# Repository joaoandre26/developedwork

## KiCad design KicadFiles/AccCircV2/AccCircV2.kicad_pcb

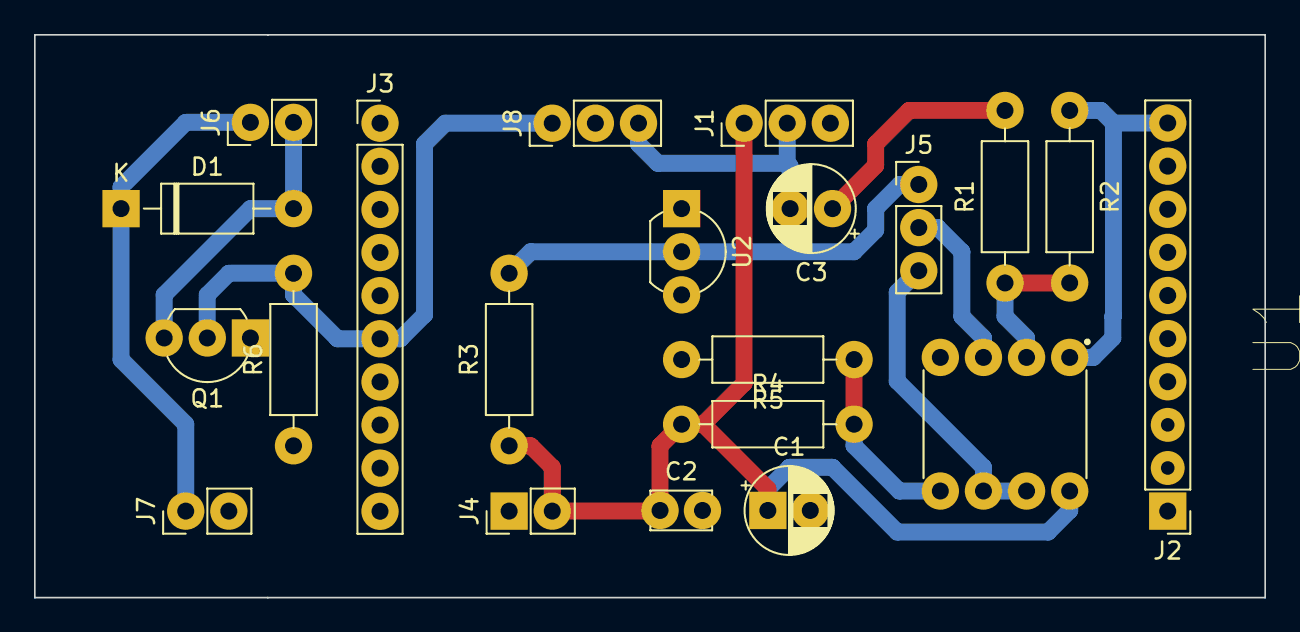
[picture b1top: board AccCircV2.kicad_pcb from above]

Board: 2 copper layers, 72.5 x 33.2 mm, 21 parts (0 on the bottom side), 13 nets.

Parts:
C1, C3: 10uF; CP_Radial_D5.0mm_P2.50mm
C2: 1nF; C_Disc_D3.4mm_W2.1mm_P2.50mm
D1: 1N4001; D_DO-41_SOD81_P10.16mm_Horizontal
J1: AccelConnector; PinHeader_1x03_P2.54mm_Vertical
J2: ADCInput; PinHeader_1x10_P2.54mm_Vertical
J3: IO; PinHeader_1x10_P2.54mm_Vertical
J4: ExternalSupply3V3; PinHeader_1x02_P2.54mm_Vertical
J5: VoltageRefSel; PinHeader_1x03_P2.54mm_Vertical
J6: Solenoid Connector; PinHeader_1x02_P2.54mm_Vertical
J7: ExternalSupply5V; PinHeader_1x02_P2.54mm_Vertical
J8: ControlSig; PinHeader_1x03_P2.54mm_Vertical
Q1: TN0207; TO-92L_Inline_Wide
R1, R2, R4, R5: R; R_Axial_DIN0207_L6.3mm_D2.5mm_P10.16mm_Horizontal
R3: 180k; R_Axial_DIN0207_L6.3mm_D2.5mm_P10.16mm_Horizontal
R6: 10k; R_Axial_DIN0207_L6.3mm_D2.5mm_P10.16mm_Horizontal
U1: MCP602; DIP787W46P254L927H533Q8
U2: LM385Z-ADJ; TO-92_Inline_Wide

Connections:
+3V3: C1.1, C2.1, J1.1, J4.2, R3.1, R4.1, U1.8
+5V: D1.1, J6.1, J7.1
AccSignal: C3.2, J1.2, J8.3
GND: C1.2, C2.2, J1.3, J3.10, J4.1, J7.2, J8.2, Q1.1, R5.2, R6.1, U1.4, U2.1, U2.3
unnamed: C3.1, R1.2
unnamed: D1.2, J6.2, Q1.3
unnamed: J2.10, R2.1, U1.1
unnamed: J5.2, U1.3
unnamed: R1.1, R2.2, U1.2
unnamed: R4.2, R5.1, U1.5
PIN3.2: J3.6, J8.1, Q1.2, R6.2
VolDivider: J5.3, U1.6, U1.7
VolRef1V2: J5.1, R3.2, U2.2

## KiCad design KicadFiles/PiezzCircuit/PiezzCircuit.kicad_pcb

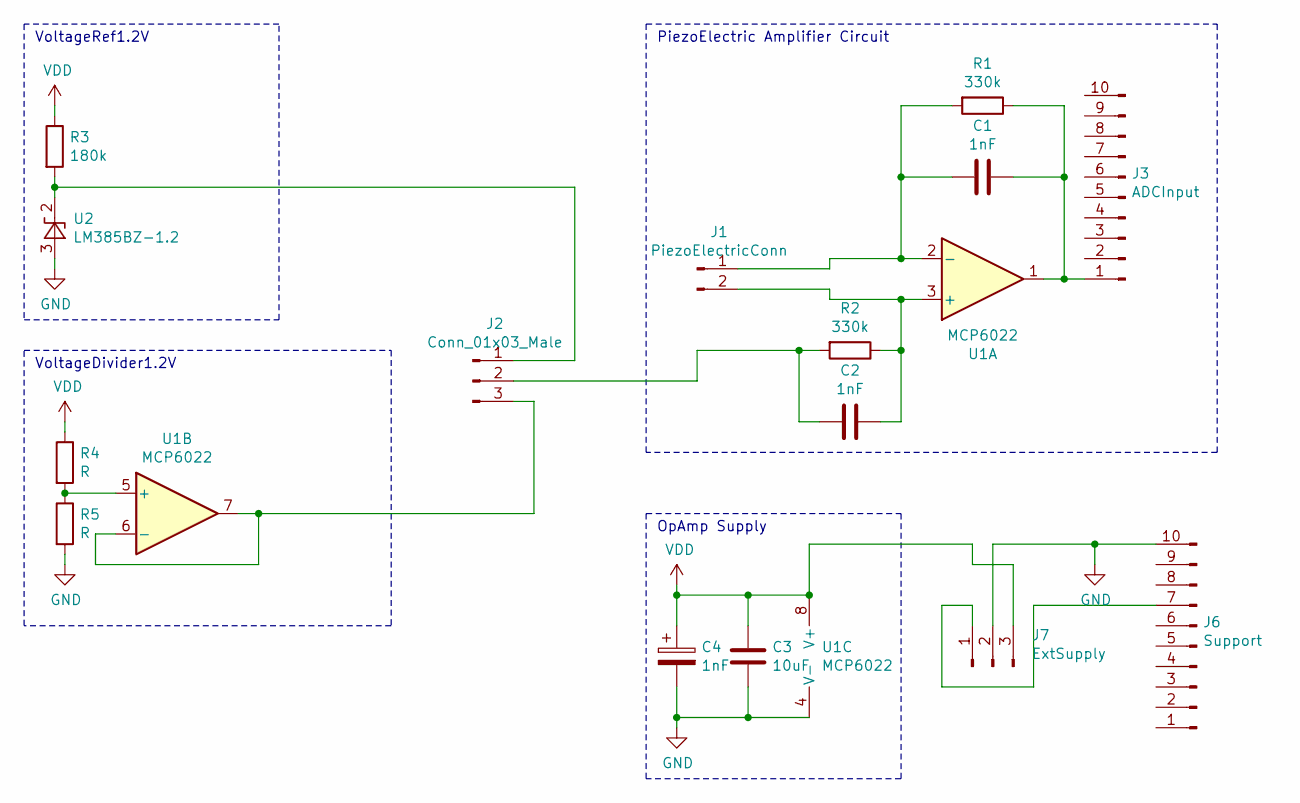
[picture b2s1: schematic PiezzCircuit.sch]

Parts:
C1, C2: 1nF; C_Rect_L4.0mm_W2.5mm_P2.50mm
C3: 10uF; C_Rect_L4.0mm_W2.5mm_P2.50mm
C4: 1nF; CP_Radial_D5.0mm_P2.00mm
J1: PiezoElectricConn; PinHeader_1x02_P2.54mm_Vertical
J2: Conn_01x03_Male; PinHeader_1x03_P2.54mm_Vertical
J3: ADCInput; PinHeader_1x10_P2.54mm_Vertical
J6: Support; PinHeader_1x10_P2.54mm_Vertical
J7: ExtSupply; PinHeader_1x03_P2.54mm_Horizontal
R1, R2: 330k; R_Axial_DIN0207_L6.3mm_D2.5mm_P10.16mm_Horizontal
R3: 180k; R_Axial_DIN0207_L6.3mm_D2.5mm_P7.62mm_Horizontal
R4, R5: R; R_Axial_DIN0207_L6.3mm_D2.5mm_P10.16mm_Horizontal
U1: MCP6022; DIP787W46P254L927H533Q8
U2: LM385BZ-1.2; TO-92_Inline

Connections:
GND: C3.2, C4.2, J6.10, J7.2, R5.2, U1.4 (V-), U2.3 (A)
unnamed: C1.1, J3.1, R1.1, U1.1
unnamed: C1.2, J1.1, R1.2, U1.2 (-)
unnamed: C2.1, J1.2, R2.1, U1.3 (+)
unnamed: C2.2, J2.2, R2.2
unnamed: J2.1, R3.2, U2.2 (K)
unnamed: J2.3, U1.6 (-), U1.7
unnamed: J6.7, J7.1
unnamed: R4.2, R5.1, U1.5 (+)
VDD: C3.1, C4.1, J7.3, R3.1, R4.1, U1.8 (V+)

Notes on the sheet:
VoltageRef1.2V
VoltageDivider1.2V
PiezoElectric Amplifier Circuit
OpAmp Supply

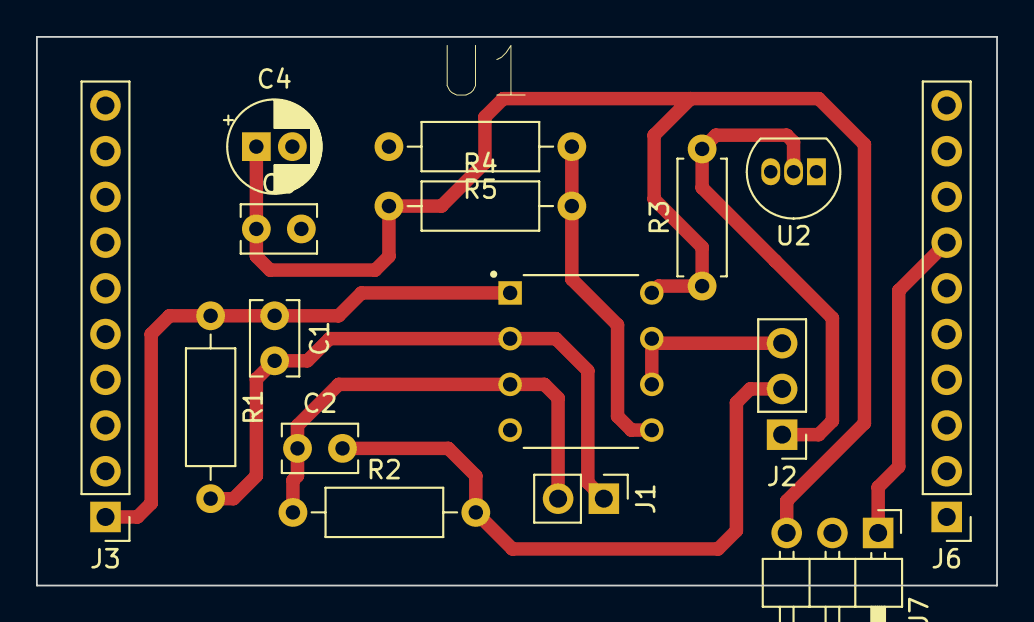
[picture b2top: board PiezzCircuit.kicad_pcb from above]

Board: 2 copper layers, 53.3 x 30.5 mm, 16 parts (0 on the bottom side), 10 nets.

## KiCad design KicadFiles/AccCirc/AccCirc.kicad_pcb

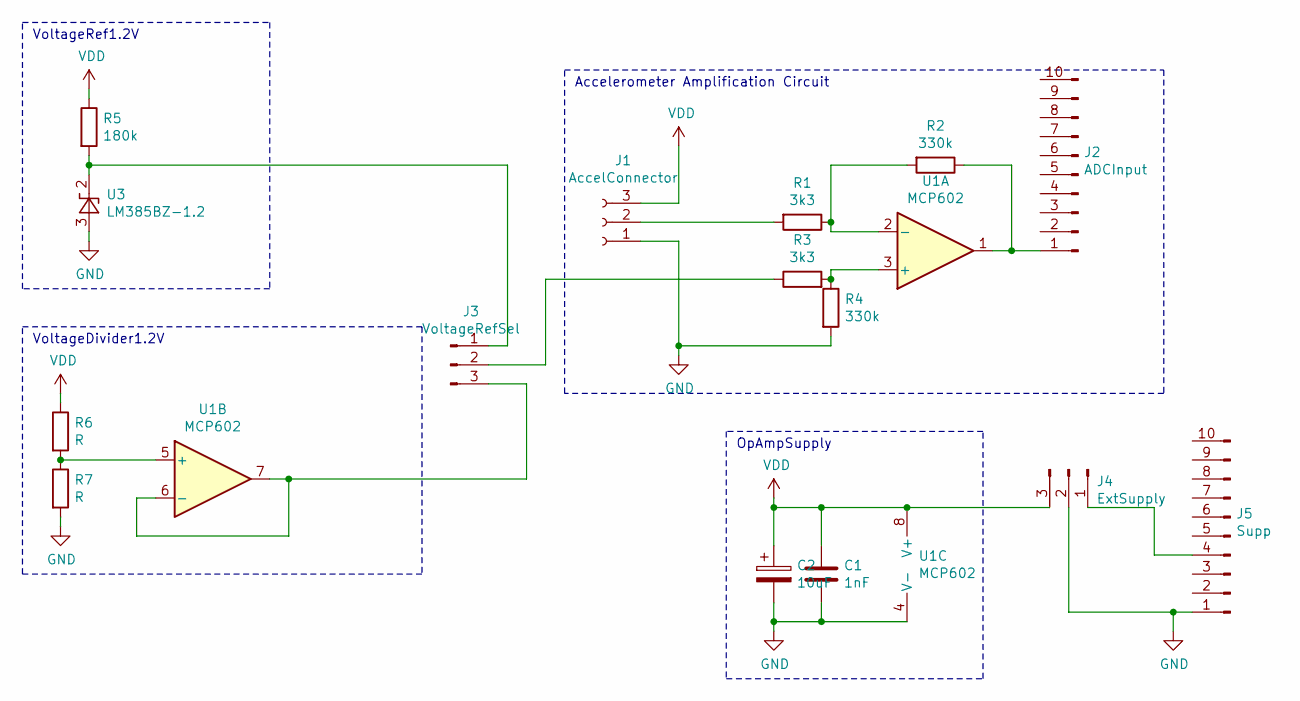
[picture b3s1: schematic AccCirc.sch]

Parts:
C1: 1nF; C_Disc_D10.5mm_W5.0mm_P5.00mm
C2: 10uF; C_Radial_D5.0mm_H11.0mm_P2.00mm
J1: AccelConnector; PinSocket_1x03_P2.54mm_Horizontal
J2: ADCInput; PinHeader_1x10_P2.54mm_Vertical
J3: VoltageRefSel; PinHeader_1x03_P2.54mm_Vertical
J4: ExtSupply; PinSocket_1x03_P2.54mm_Horizontal
J5: Supp; PinHeader_1x10_P2.54mm_Vertical
R1, R3: 3k3; R_Axial_DIN0207_L6.3mm_D2.5mm_P10.16mm_Horizontal
R2, R4: 330k; R_Axial_DIN0207_L6.3mm_D2.5mm_P10.16mm_Horizontal
R5: 180k; R_Axial_DIN0207_L6.3mm_D2.5mm_P10.16mm_Horizontal
R6, R7: R; R_Axial_DIN0207_L6.3mm_D2.5mm_P10.16mm_Horizontal
U1: MCP602; DIP787W46P254L927H533Q8
U3: LM385BZ-1.2; TO-92_Inline

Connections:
GND: C1.2, C2.2, J1.1, J4.2, J5.1, R4.2, R7.2, U1.4 (V-), U3.3 (A)
unnamed: J1.2, R1.2
unnamed: J2.1, R2.1, U1.1
unnamed: J3.1, R5.2, U3.2 (K)
unnamed: J3.2, R3.1
unnamed: J3.3, U1.6 (-), U1.7
unnamed: J4.1, J5.4
unnamed: R1.1, R2.2, U1.2 (-)
unnamed: R3.2, R4.1, U1.3 (+)
unnamed: R6.2, R7.1, U1.5 (+)
VDD: C1.1, C2.1, J1.3, J4.3, R5.1, R6.1, U1.8 (V+)

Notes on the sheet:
Accelerometer Amplification Circuit
VoltageRef1.2V
VoltageDivider1.2V
OpAmpSupply

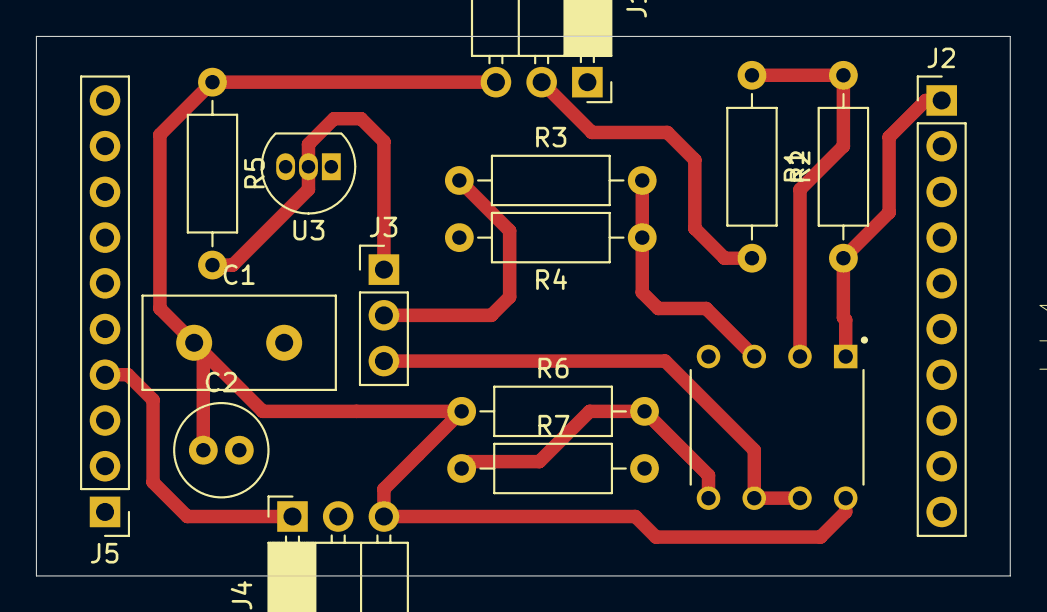
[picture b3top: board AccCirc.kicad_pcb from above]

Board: 2 copper layers, 54.1 x 30.0 mm, 16 parts (0 on the bottom side), 11 nets.

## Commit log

2020-09-08 first commit + developed work till today
2020-09-09 Mat Script update
2020-09-09 New tests
2020-12-10 Recent Updates
2020-12-10 New files
2020-12-22 some updates
2021-01-05 new changes
2021-01-12 New project and some updates
2021-01-27 Added a project to manual hit, with a interval distance
2021-04-19 New project CCS
2021-04-20 new device drivers
2021-04-22 new proj manual
2021-05-17 changes in level id code
2021-06-03 some changes
2021-06-09 some scripts to export graphics
2021-07-10 apresentação
2021-07-10 ate hw feito
2021-07-14 Presentation almost done
2021-07-19 Presentatio almost finished
